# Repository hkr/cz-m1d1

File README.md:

# cz-m1d1
Alternative CZ-6BM1

Board cuts and footprints are from Midiori project.
Some footprints and symbols are downloaded from Digikey and/or Mouser.

## Testing status

### tested:
- MIDI out
- MIDI through/out2 switch
- MIDI through
- MIDI in only as part of MIDI through test

### untested:
- tape sync
- address and interrupt configurarion

## Changelog

- mk1 initial prototype
- mk2 change board design to match the look of the original CZ-6BM1
- minor silkscreen fix after that, but I have not built a card with it

## Pics

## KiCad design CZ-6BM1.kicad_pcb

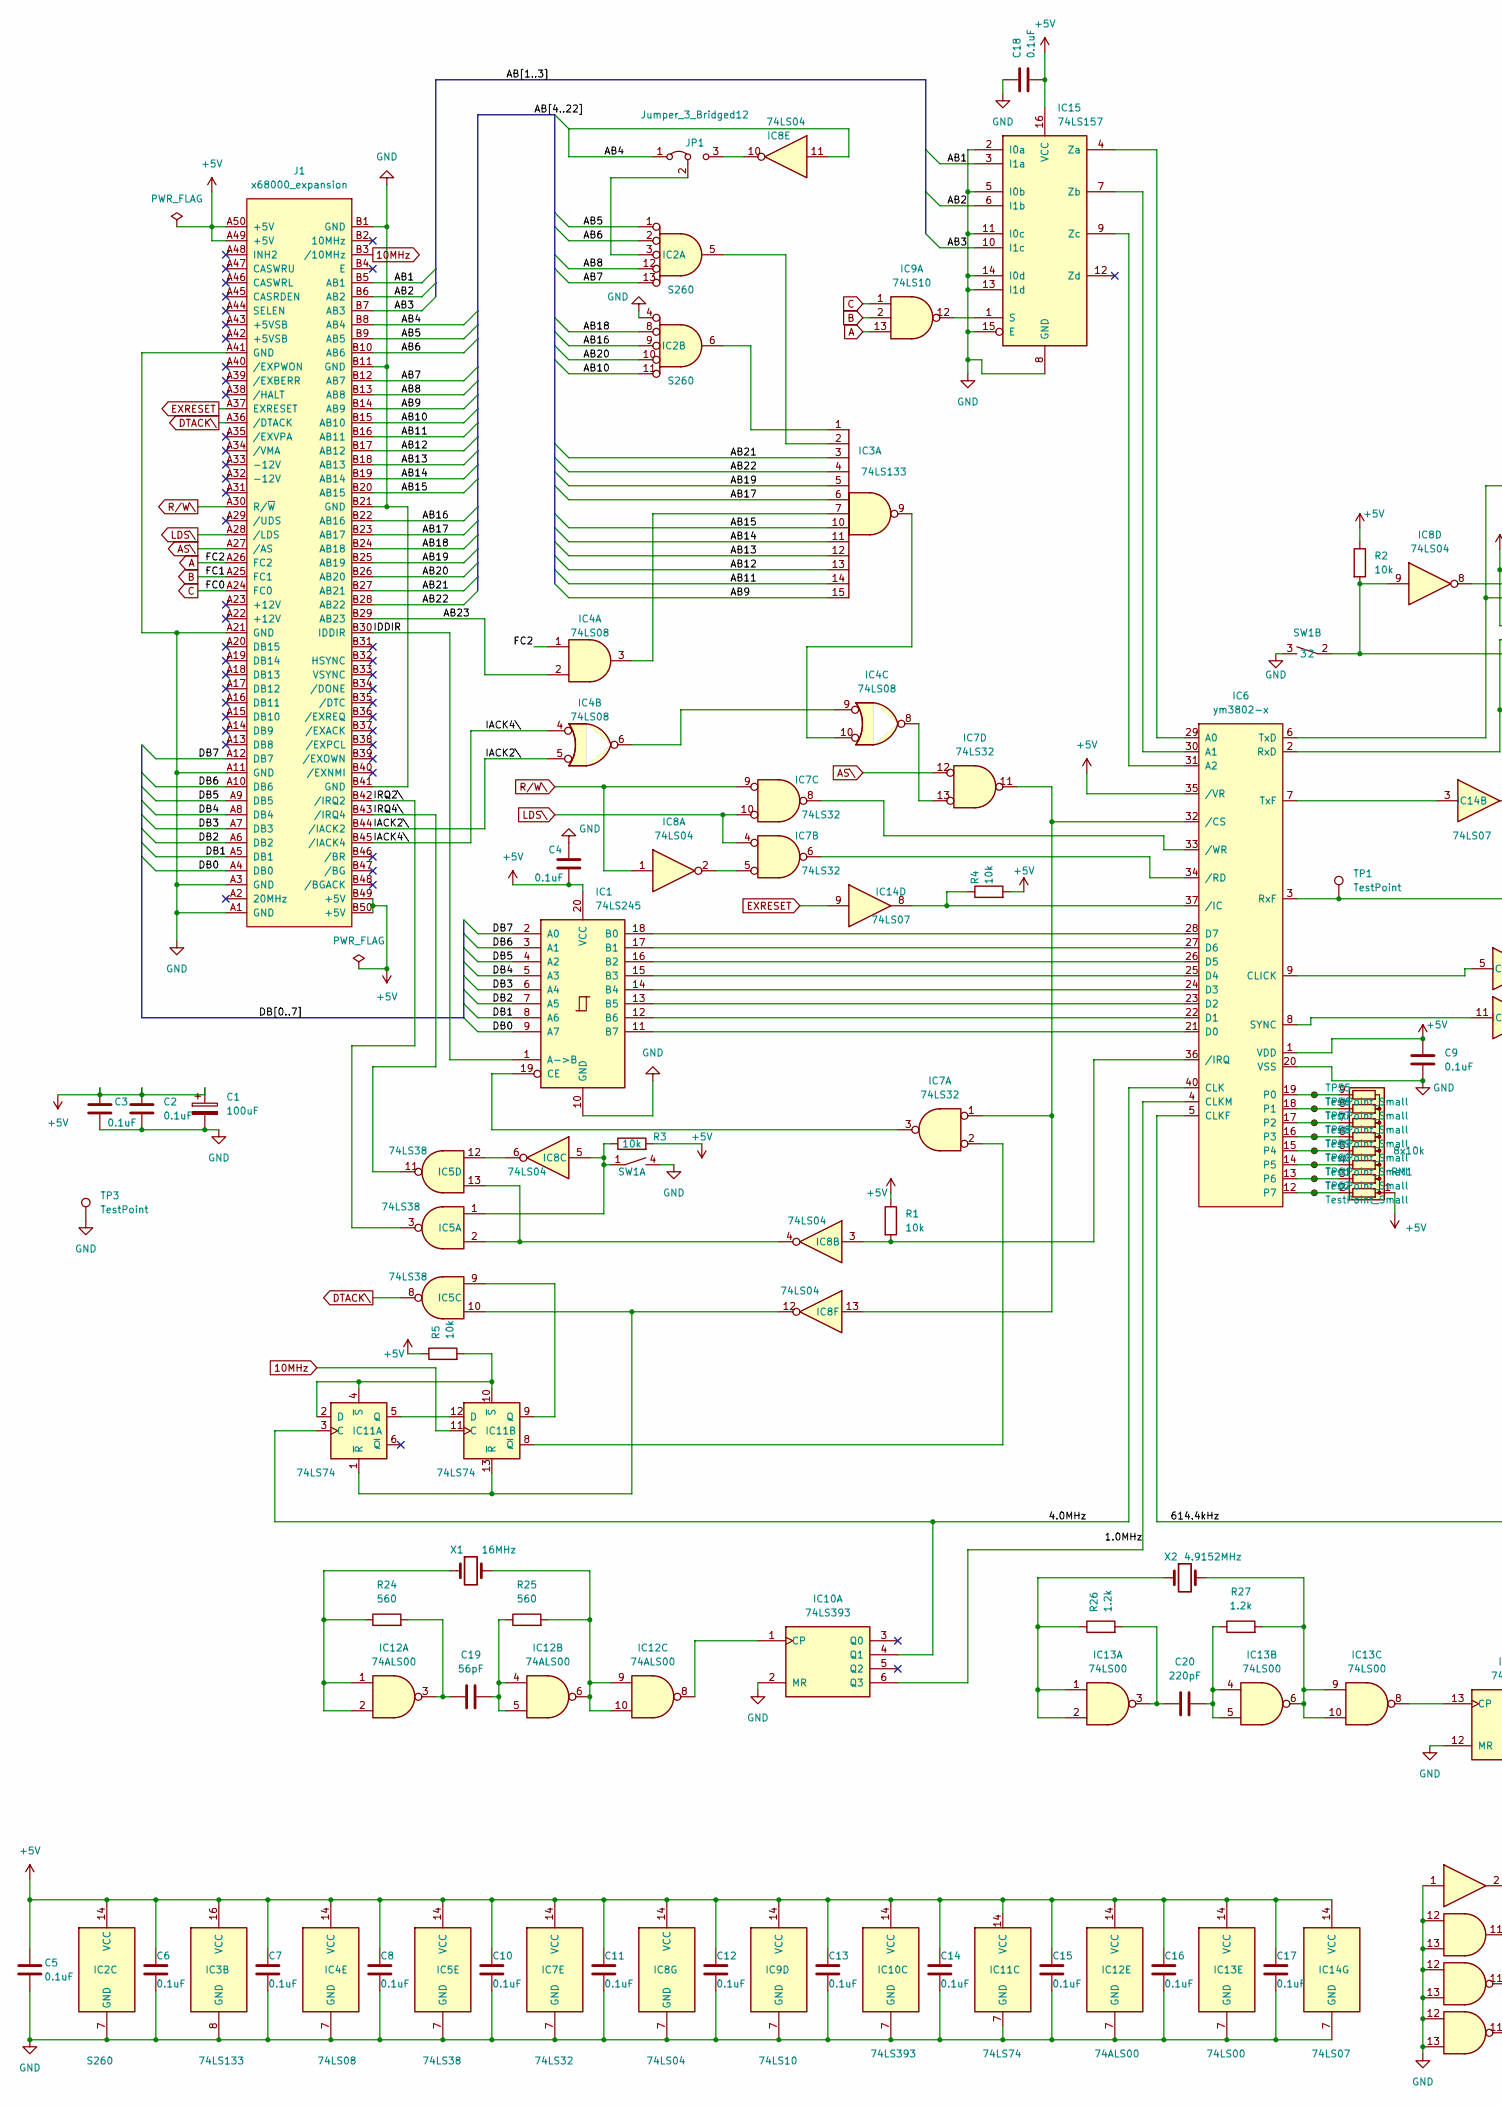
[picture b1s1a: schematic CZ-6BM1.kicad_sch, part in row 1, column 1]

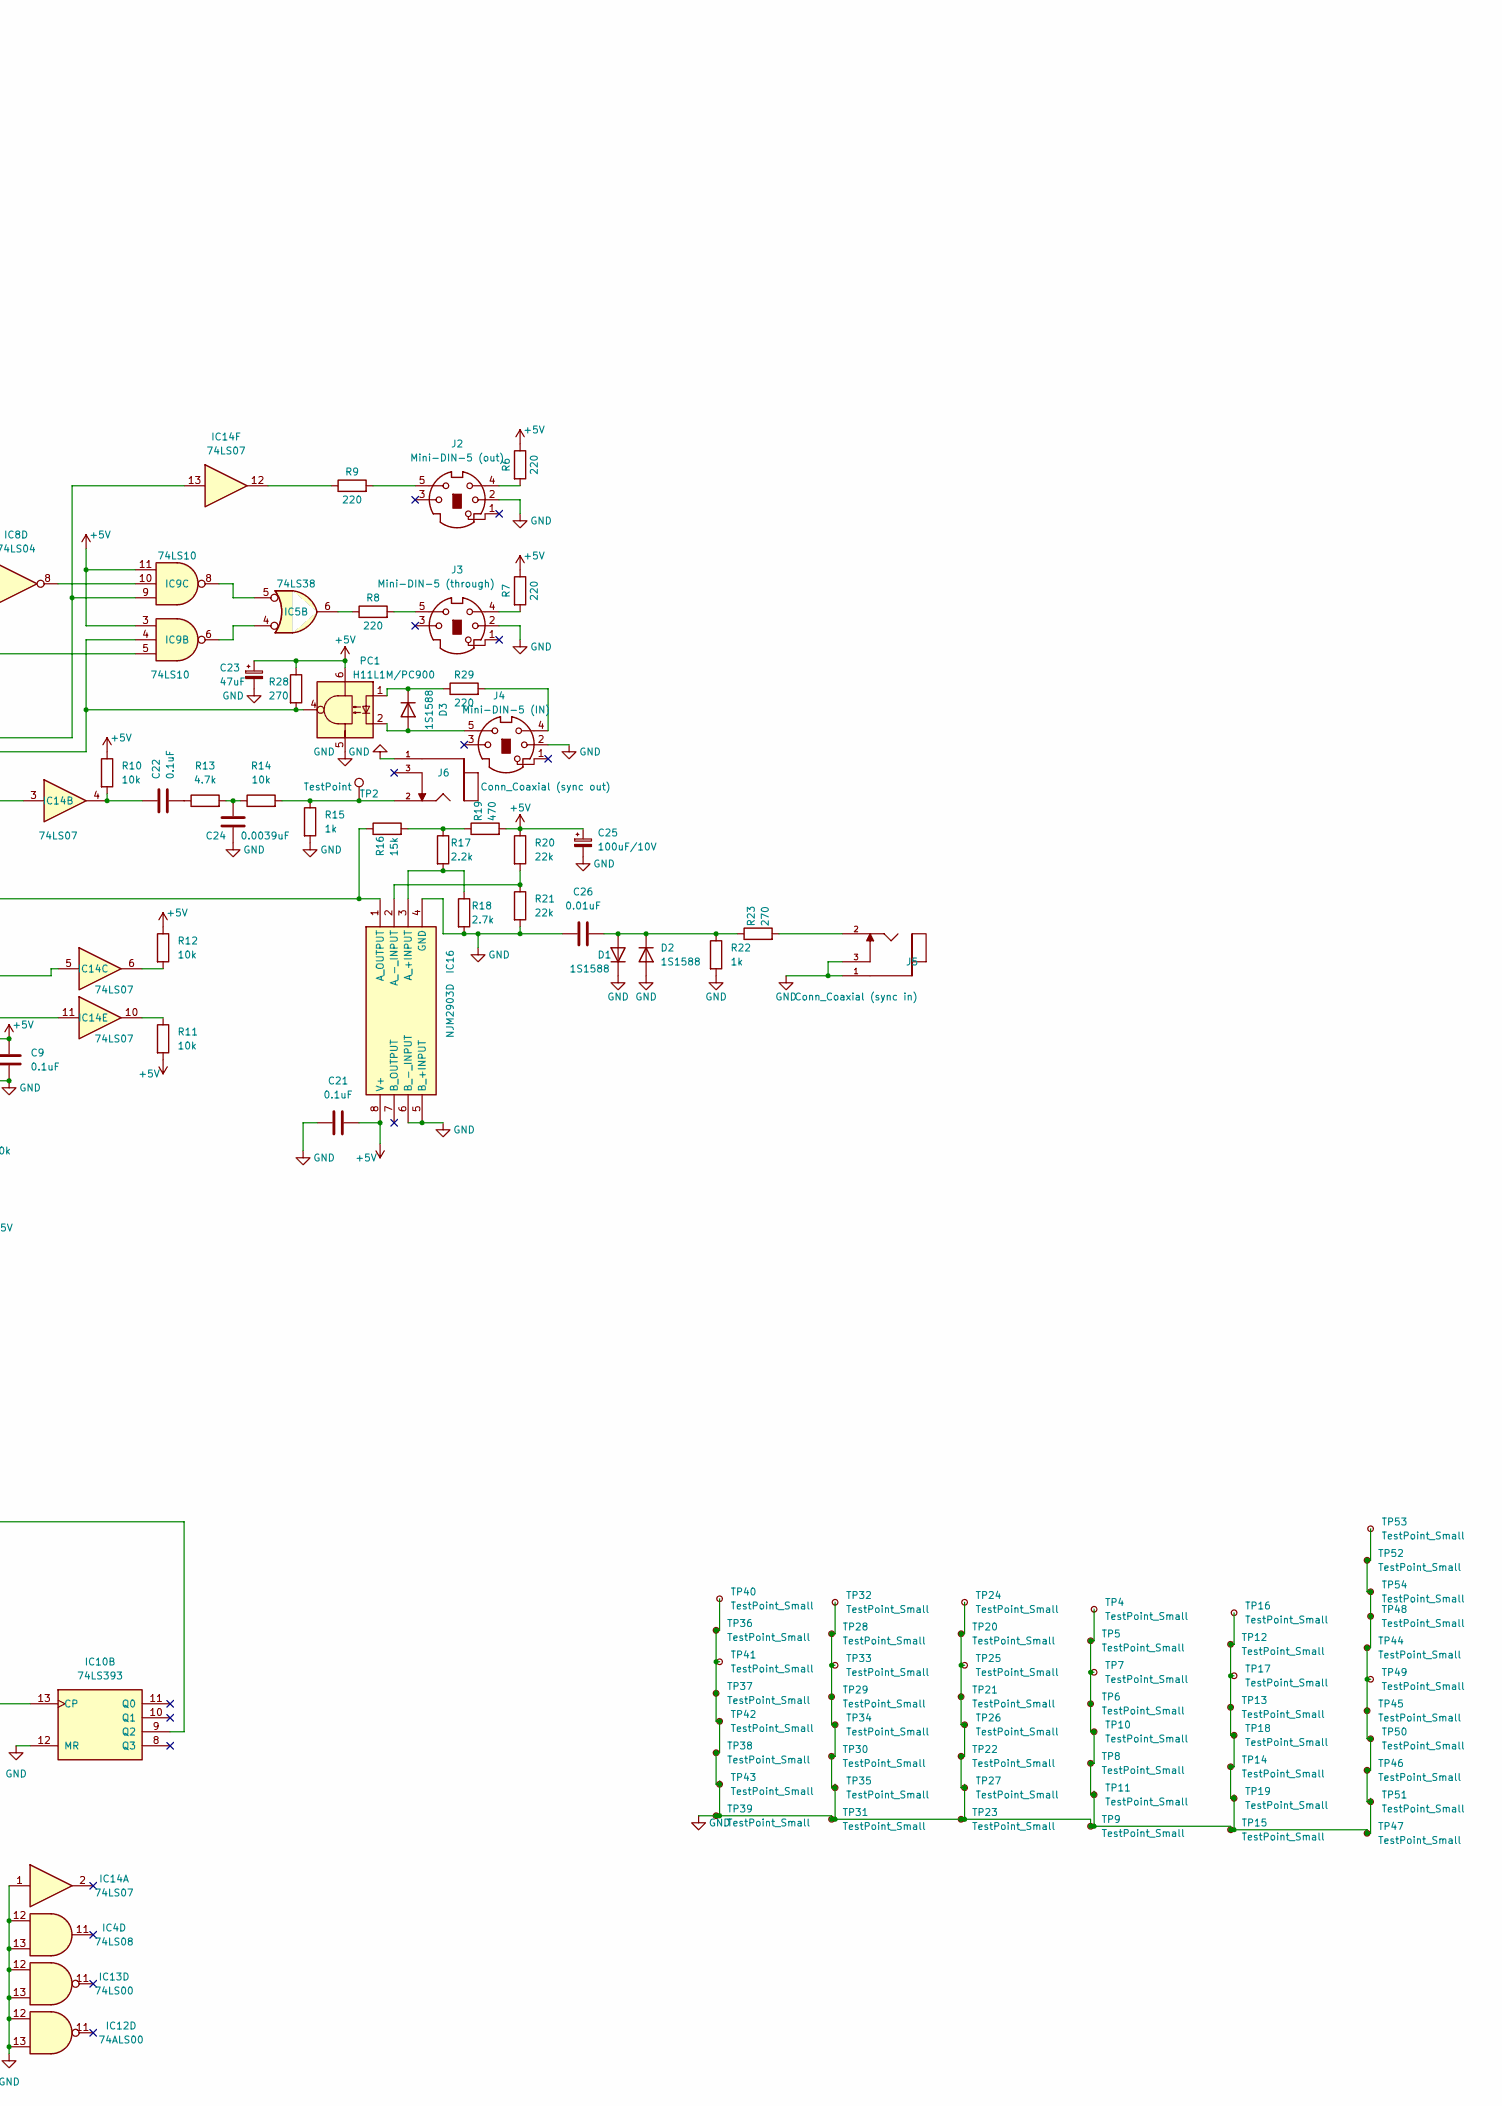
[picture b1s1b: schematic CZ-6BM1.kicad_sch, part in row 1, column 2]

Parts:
C1: 100uF; CP_Radial_D6.3mm_P2.50mm
C2, C3, C4, C5, C6, C7, C8, C9, C10, C11, C12, C13, C14, C15, C16, C17, C18, C21: 0.1uF; C_Rect_L7.0mm_W2.5mm_P5.00mm
C19: 56pF; C_Rect_L4.0mm_W2.5mm_P2.50mm
C20: 220pF; C_Rect_L4.0mm_W2.5mm_P2.50mm
C22: 0.1uF; ECQE2104JB
C23: 47uF; CP_Radial_D6.3mm_P2.50mm
C24: 0.0039uF; CAP_QYX_3P5X6X8P5_NCH
C25: 100uF/10V; CP_Radial_D6.3mm_P2.50mm
C26: 0.01uF; CAP_QYX_3P5X6X8P5_NCH
D1, D2, D3: 1S1588; D_DO-35_SOD27_P7.62mm_Horizontal
IC1: 74LS245; DIP-20_W7.62mm
IC2: S260; DIP-14_W7.62mm
IC3: 74LS133; DIP-16_W7.62mm
IC4: 74LS08; DIP-14_W7.62mm
IC5: 74LS38; DIP-14_W7.62mm
IC6: ym3802-x; DIP-40_W15.24mm
IC7: 74LS32; DIP-14_W7.62mm
IC8: 74LS04; DIP-14_W7.62mm
IC9: 74LS10; DIP-14_W7.62mm
IC10: 74LS393; DIP-14_W7.62mm
IC11: 74LS74; DIP-14_W7.62mm
IC12: 74ALS00; DIP-14_W7.62mm
IC13: 74LS00; DIP-14_W7.62mm
IC14: 74LS07; DIP-14_W7.62mm
IC15: 74LS157; DIP-16_W7.62mm
IC16: NJM2903D; DIP762W56P254L880H425Q8N; Mouser Part Number 513-NJM2903D
J1: x68000_expansion
J2: Mini-DIN-5 (out); MD-50SM
J3: Mini-DIN-5 (through); MD-50SM
J4: Mini-DIN-5 (IN); MD-50SM
J5: Conn_Coaxial (sync in); SWITCHCRAFT_PJRAN1X1U01X; PART_REV B
J6: Conn_Coaxial (sync out); SWITCHCRAFT_PJRAN1X1U01X; PART_REV B
JP1: Jumper_3_Bridged12; PinHeader_1x03_P2.54mm_Vertical
PC1: H11L1M/PC900; DIP-6_W7.62mm
R1, R2, R3, R4, R5, R10, R11, R12, R14: 10k; R_Axial_DIN0204_L3.6mm_D1.6mm_P5.08mm_Horizontal
R6, R7, R8, R9, R29: 220; R_Axial_DIN0204_L3.6mm_D1.6mm_P5.08mm_Horizontal
R13: 4.7k; R_Axial_DIN0204_L3.6mm_D1.6mm_P5.08mm_Horizontal
R15, R22: 1k; R_Axial_DIN0204_L3.6mm_D1.6mm_P5.08mm_Horizontal
R16: 15k; R_Axial_DIN0204_L3.6mm_D1.6mm_P5.08mm_Horizontal
R17: 2.2k; R_Axial_DIN0204_L3.6mm_D1.6mm_P5.08mm_Horizontal
R18: 2.7k; R_Axial_DIN0204_L3.6mm_D1.6mm_P5.08mm_Horizontal
R19: 470; R_Axial_DIN0204_L3.6mm_D1.6mm_P5.08mm_Horizontal
R20, R21: 22k; R_Axial_DIN0204_L3.6mm_D1.6mm_P5.08mm_Horizontal
R23, R28: 270; R_Axial_DIN0204_L3.6mm_D1.6mm_P5.08mm_Horizontal
R24, R25: 560; R_Axial_DIN0204_L3.6mm_D1.6mm_P5.08mm_Horizontal
R26, R27: 1.2k; R_Axial_DIN0204_L3.6mm_D1.6mm_P5.08mm_Horizontal
RM1: 8x10k; R_Array_SIP9
SW1: SW_DIP_SPSTx02_Slide_9.78x7.26mm_W7.62mm_P2.54mm
TP1, TP2, TP3: TestPoint; TestPoint_Loop_D2.50mm_Drill1.0mm
TP4, TP5, TP6, TP7, TP8, TP9, TP10, TP11, TP12, TP13, TP14, TP15, TP16, TP17, TP18, TP19, TP20, TP21, TP22, TP23, TP24, TP25, TP26, TP27, TP28, TP29, TP30, TP31, TP32, TP33, TP34, TP35, TP36, TP37, TP38, TP39, TP40, TP41, TP42, TP43, TP44, TP45, TP46, TP47, TP48, TP49, TP50, TP51, TP52, TP53, TP54, TP55, TP56, TP57, TP58, TP59, TP60, TP61, TP62: TestPoint_Small; TestPoint_THTPad_D1.0mm_Drill0.5mm
X1: 16MHz; Crystal_HC49-U_Horizontal_1EP_style2
X2: 4.9152MHz; Crystal_HC49-U_Horizontal_1EP_style2

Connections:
10MHz: IC11.11 (C), J1.B3 (/10MHz)
+5V: C1.1, C2.1, C3.1, C4.2, C5.1, C6.1, C7.1, C8.1, C9.1, C10.1, C11.1, C12.1, C13.1, C14.1, C15.1, C16.1, C17.1, C18.2, C21.2, C23.1, C25.1, IC1.20 (VCC), IC2.14 (VCC), IC3.16 (VCC), IC4.14 (VCC), IC5.14 (VCC), IC6.1 (VDD), IC6.35 (/VR), IC7.14 (VCC), IC8.14 (VCC), IC9.3, IC9.11, IC9.14 (VCC), IC10.14 (VCC), IC11.14 (VCC), IC12.14 (VCC), IC13.14 (VCC), IC14.14 (VCC), IC15.16 (VCC), IC16.8 (V+), J1.A49 (+5V), J1.A50 (+5V), J1.B49 (+5V), J1.B50 (+5V), PC1.6, R1.1, R2.1, R3.2, R4.2, R5.1, R6.1, R7.1, R10.1, R11.2, R12.1, R19.2, R20.1, R28.1, RM1.1 (common)
/1.0MHz: IC6.4 (CLKM), IC10.6 (Q3)
/4.0MHz: IC6.40 (CLK), IC10.4 (Q1), IC11.3 (C)
/614.4kHz: IC6.5 (CLKF), IC10.9 (Q2)
/AB1: IC15.3 (I1a), J1.B5 (AB1)
/AB2: IC15.6 (I1b), J1.B6 (AB2)
/AB3: IC15.10 (I1c), J1.B7 (AB3)
/AB4: IC8.11, J1.B8 (AB4), JP1.1 (A)
/AB5: IC2.1, J1.B9 (AB5)
/AB6: IC2.2, J1.B10 (AB6)
/AB7: IC2.13, J1.B12 (AB7)
/AB8: IC2.12, J1.B13 (AB8)
/AB9: IC3.15, J1.B14 (AB9)
/AB10: IC2.11, J1.B15 (AB10)
/AB11: IC3.14, J1.B16 (AB11)
/AB12: IC3.13, J1.B17 (AB12)
/AB13: IC3.12, J1.B18 (AB13)
/AB14: IC3.11, J1.B19 (AB14)
/AB15: IC3.10, J1.B20 (AB15)
/AB16: IC2.9, J1.B22 (AB16)
/AB17: IC3.6, J1.B23 (AB17)
/AB18: IC2.8, J1.B24 (AB18)
/AB19: IC3.5, J1.B25 (AB19)
/AB20: IC2.10, J1.B26 (AB20)
/AB21: IC3.3, J1.B27 (AB21)
/AB22: IC3.4, J1.B28 (AB22)
/AB23: IC4.2, J1.B29 (AB23)
/DB0: IC1.9 (A7), J1.A4 (DB0)
/DB1: IC1.8 (A6), J1.A5 (DB1)
/DB2: IC1.7 (A5), J1.A6 (DB2)
/DB3: IC1.6 (A4), J1.A7 (DB3)
/DB4: IC1.5 (A3), J1.A8 (DB4)
/DB5: IC1.4 (A2), J1.A9 (DB5)
/DB6: IC1.3 (A1), J1.A10 (DB6)
/DB7: IC1.2 (A0), J1.A12 (DB7)
/IACK2\: IC4.5, J1.B44 (/IACK2)
/IACK4\: IC4.4, J1.B45 (/IACK4)
/IDDIR: IC1.1 (A->B), J1.B30 (IDDIR)
/IRQ2\: IC5.3, J1.B42 (/IRQ2)
/IRQ4\: IC5.11, J1.B43 (/IRQ4)
A: IC4.1, IC9.13, J1.A26 (FC2)
AS\: IC7.12, J1.A27 (/AS)
B: IC9.2, J1.A25 (FC1)
C: IC9.1, J1.A24 (FC0)
DTACK\: IC5.8, J1.A36 (/DTACK)
EXRESET: IC14.9, J1.A37 (EXRESET)
GND: C1.2, C2.2, C3.2, C4.1, C5.2, C6.2, C7.2, C8.2, C9.2, C10.2, C11.2, C12.2, C13.2, C14.2, C15.2, C16.2, C17.2, C18.1, C21.1, C23.2, C24.2, C25.2, C26.1, D1.1 (K), D2.2 (A), IC1.10 (GND), IC2.4, IC2.7 (GND), IC3.8 (GND), IC4.7 (GND), IC4.12, IC4.13, IC5.7 (GND), IC6.20 (VSS), IC7.7 (GND), IC8.7 (GND), IC9.7 (GND), IC10.2 (MR), IC10.7 (GND), IC10.12 (MR), IC11.7 (GND), IC12.7 (GND), IC12.12, IC12.13, IC13.7 (GND), IC13.12, IC13.13, IC14.1, IC14.7 (GND), IC15.2 (I0a), IC15.5 (I0b), IC15.8 (GND), IC15.11 (I0c), IC15.13 (I1d), IC15.14 (I0d), IC15.15 (E), IC16.4 (GND), IC16.5 (B_+INPUT), IC16.6 (B_-_INPUT), J1.A1 (GND), J1.A3 (GND), J1.A11 (GND), J1.A21 (GND), J1.A41 (GND), J1.B1 (GND), J1.B11 (GND), J1.B21 (GND), J1.B41 (GND), J2.2, J3.2, J4.2, J5.1, J5.3, J6.1, PC1.5, R15.2, R18.2, R21.2, R22.2, SW1.3, SW1.4, TP3.1, TP4.1, TP5.1, TP6.1, TP7.1, TP8.1, TP9.1, TP10.1, TP11.1, TP12.1, TP13.1, TP14.1, TP15.1, TP16.1, TP17.1, TP18.1, TP19.1, TP20.1, TP21.1, TP22.1, TP23.1, TP24.1, TP25.1, TP26.1, TP27.1, TP28.1, TP29.1, TP30.1, TP31.1, TP32.1, TP33.1, TP34.1, TP35.1, TP36.1, TP37.1, TP38.1, TP39.1, TP40.1, TP41.1, TP42.1, TP43.1, TP44.1, TP45.1, TP46.1, TP47.1, TP48.1, TP49.1, TP50.1, TP51.1, TP52.1, TP53.1, TP54.1
LDS\: IC7.4, IC7.10, J1.A28 (/LDS)
unnamed: C19.1, IC12.3, R24.2
unnamed: C19.2, IC12.4, IC12.5, R25.1
unnamed: C20.1, IC13.3, R26.2
unnamed: C20.2, IC13.4, IC13.5, R27.1
unnamed: C22.1, IC14.4, R10.2
unnamed: C22.2, R13.1
unnamed: C24.1, R13.2, R14.1
unnamed: C26.2, D1.2 (A), D2.1 (K), R22.1, R23.1
unnamed: D3.2 (A), J4.5, PC1.2
unnamed: D3.1 (K), PC1.1, R29.1
unnamed: IC1.18 (B0), IC6.28 (D7)
unnamed: IC1.17 (B1), IC6.27 (D6)
unnamed: IC1.16 (B2), IC6.26 (D5)
unnamed: IC1.15 (B3), IC6.25 (D4)
unnamed: IC1.14 (B4), IC6.24 (D3)
unnamed: IC1.13 (B5), IC6.23 (D2)
unnamed: IC1.12 (B6), IC6.22 (D1)
unnamed: IC1.11 (B7), IC6.21 (D0)
unnamed: IC1.19 (CE), IC7.3
unnamed: IC2.5, IC3.2
unnamed: IC2.6, IC3.1
unnamed: IC3.7, IC4.3
unnamed: IC3.9, IC4.10
unnamed: IC4.6, IC4.9
unnamed: IC4.8, IC7.13
unnamed: IC5.1, IC8.5, R3.1, SW1.1
unnamed: IC5.4, IC9.6
unnamed: IC5.5, IC9.8
unnamed: IC5.6, R8.1
unnamed: IC5.12, IC8.6
unnamed: IC5.2, IC5.13, IC8.4
unnamed: IC6.9 (CLICK), IC14.5
unnamed: IC6.19 (P0), RM1.9 (R8), TP55.1
unnamed: IC6.18 (P1), RM1.8 (R7), TP56.1
unnamed: IC6.17 (P2), RM1.7 (R6), TP57.1
unnamed: IC6.16 (P3), RM1.6 (R5), TP58.1
unnamed: IC6.15 (P4), RM1.5 (R4), TP59.1
unnamed: IC6.14 (P5), RM1.4 (R3), TP60.1
unnamed: IC6.13 (P6), RM1.3 (R2), TP61.1
unnamed: IC6.12 (P7), RM1.2 (R1), TP62.1
unnamed: IC6.2 (RxD), IC9.4, PC1.4, R28.2
unnamed: IC6.8 (SYNC), IC14.11
unnamed: IC6.6 (TxD), IC9.9, IC14.13
unnamed: IC6.7 (TxF), IC14.3
unnamed: IC6.32 (/CS), IC7.1, IC7.11, IC8.13
unnamed: IC6.37 (/IC), IC14.8, R4.1
unnamed: IC6.36 (/IRQ), IC8.3, R1.2
unnamed: IC6.34 (/RD), IC7.6
unnamed: IC6.33 (/WR), IC7.8
unnamed: IC7.5, IC8.2
unnamed: IC8.8, IC9.10
unnamed: IC8.9, IC9.5, R2.2, SW1.2
unnamed: IC10.1 (CP), IC12.8
unnamed: IC10.13 (CP), IC13.8
unnamed: IC11.2 (D), IC11.4 (~S), IC11.10 (~S), R5.2
unnamed: IC11.5 (Q), IC11.12 (D)
unnamed: IC5.10, IC8.12, IC11.1 (~R), IC11.13 (~R)
unnamed: IC5.9, IC11.9 (Q)
unnamed: IC7.2, IC11.8 (~Q)
unnamed: IC12.1, IC12.2, R24.1, X1.1
unnamed: IC12.6, IC12.9, IC12.10, R25.2, X1.2
unnamed: IC13.1, IC13.2, R26.1, X2.1
unnamed: IC13.6, IC13.9, IC13.10, R27.2, X2.2
unnamed: IC14.6, R12.2
unnamed: IC14.10, R11.1
unnamed: IC14.12, R9.1
unnamed: IC9.12, IC15.1 (S)
unnamed: IC6.29 (A0), IC15.4 (Za)
unnamed: IC6.30 (A1), IC15.7 (Zb)
unnamed: IC6.31 (A2), IC15.9 (Zc)
unnamed: IC16.3 (A_+INPUT), R17.2, R18.1
unnamed: IC16.2 (A_-_INPUT), R20.2, R21.1
unnamed: IC6.3 (RxF), IC16.1 (A_OUTPUT), R16.1, TP1.1
unnamed: J2.4, R6.2
unnamed: J2.5, R9.2
unnamed: J3.4, R7.2
unnamed: J3.5, R8.2
unnamed: J4.4, R29.2
unnamed: J5.2, R23.2
unnamed: J6.2, R14.2, R15.1, TP2.1
unnamed: IC8.10, JP1.3 (B)
unnamed: IC2.3, JP1.2 (C)
unnamed: R16.2, R17.1, R19.1
R/W\: IC7.9, IC8.1, J1.A30 (R/~W)

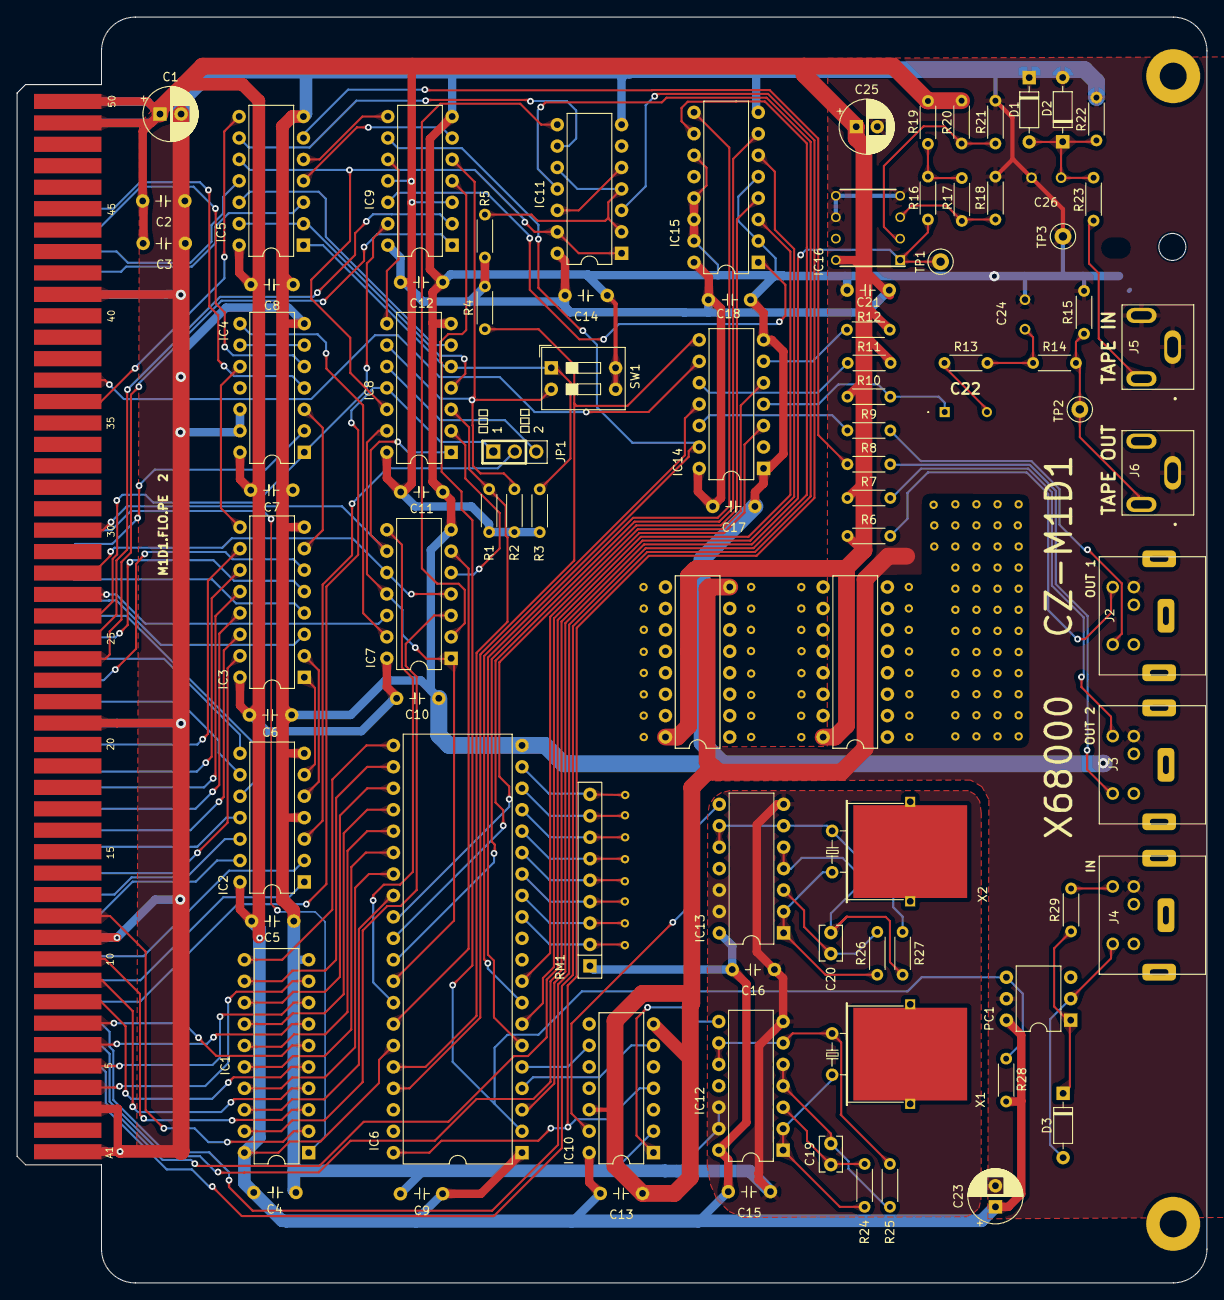
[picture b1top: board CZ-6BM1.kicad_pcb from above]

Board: 2 copper layers, 141.0 x 150.0 mm, 179 parts (0 on the bottom side), 133 nets.

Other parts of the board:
H1, H2: MountingHole; MountingHole_3.2mm_M3_Pad
TP45#2, TP45#3, TP45#4, TP45#5, TP45#6, TP45#7, TP45#8, TP45#9, TP45#10, TP45#11, TP45#12, TP45#13, TP45#14, TP45#15, TP45#16, TP45#17, TP45#18, TP45#19, TP45#20, TP45#21, TP45#22, TP45#23, TP45#24, TP45#25, TP45#26, TP45#27, TP45#28, TP45#29, TP45#30: TestPoint_Small; TestPoint_THTPad_D1.0mm_Drill0.5mm

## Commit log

2024-02-24 Silkscreen fix
2024-02-24 Add readme and photo of card
2024-02-28 Added cover plate Based on https://www.thingiverse.com/thing:2582761
2024-02-28 Update README.md
    Fix typo
